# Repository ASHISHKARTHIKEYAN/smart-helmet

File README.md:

View this project on [CADLAB.io](https://cadlab.io/project/29150). 

# smart-helmet

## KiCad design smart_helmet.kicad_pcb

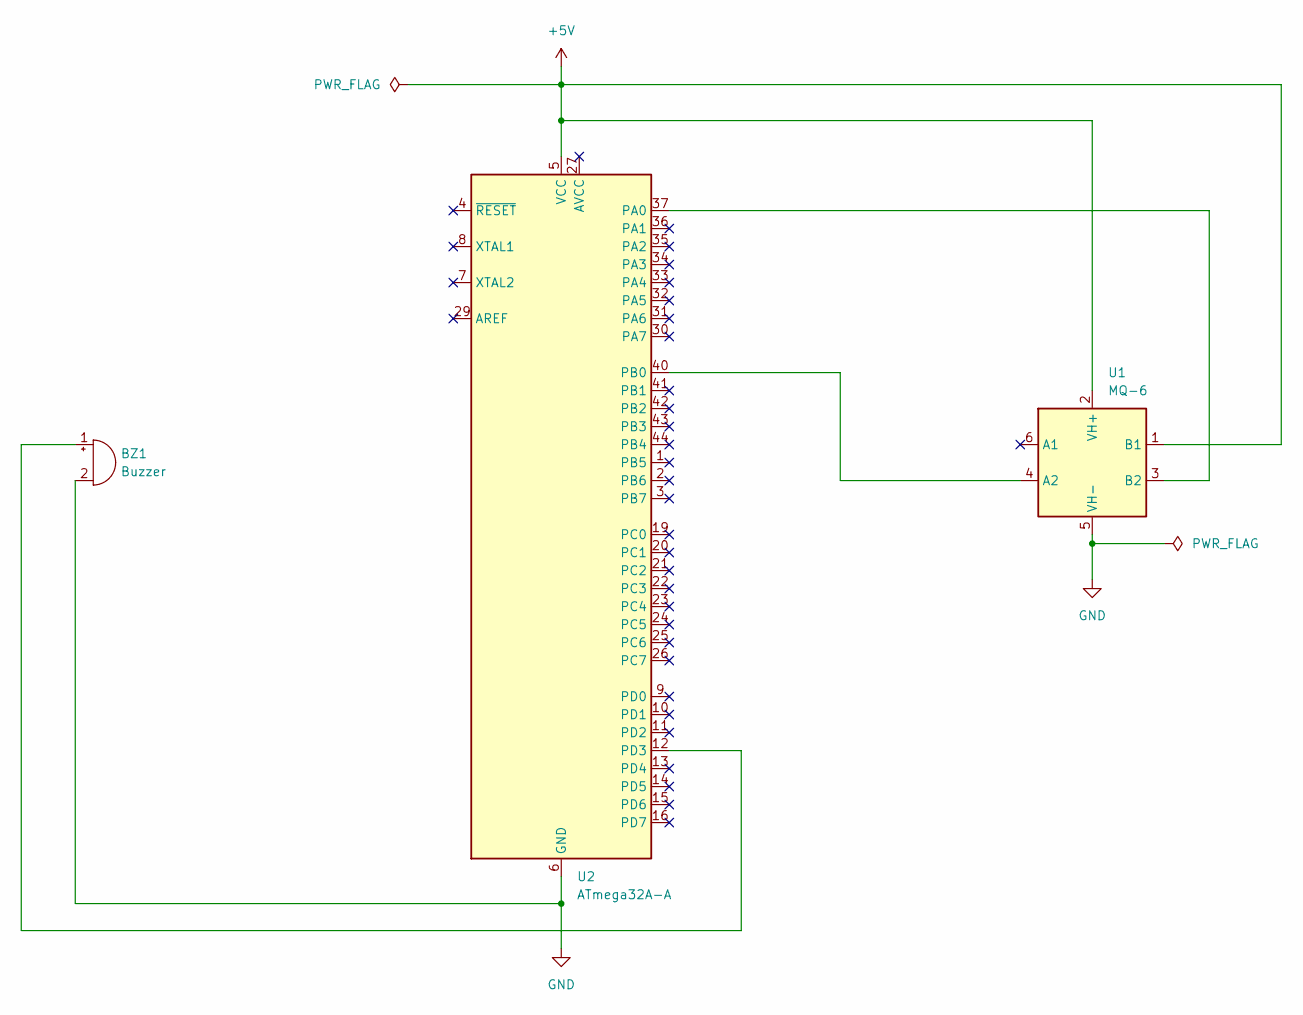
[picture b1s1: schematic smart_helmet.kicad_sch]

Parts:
BZ1: Buzzer; Buzzer_12x9.5RM7.6
U1: MQ-6
U2: ATmega32A-A; TQFP-44_10x10mm_P0.8mm

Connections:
+5V: U1.1 (B1), U1.2 (VH+), U2.5 (VCC), U2.17 (VCC), U2.38 (VCC)
GND: BZ1.2 (-), U1.5 (VH-), U2.6 (GND), U2.18 (GND), U2.28 (GND), U2.39 (GND)
unnamed: BZ1.1 (+), U2.12 (PD3)
unnamed: U1.4 (A2), U2.40 (PB0)
unnamed: U1.3 (B2), U2.37 (PA0)

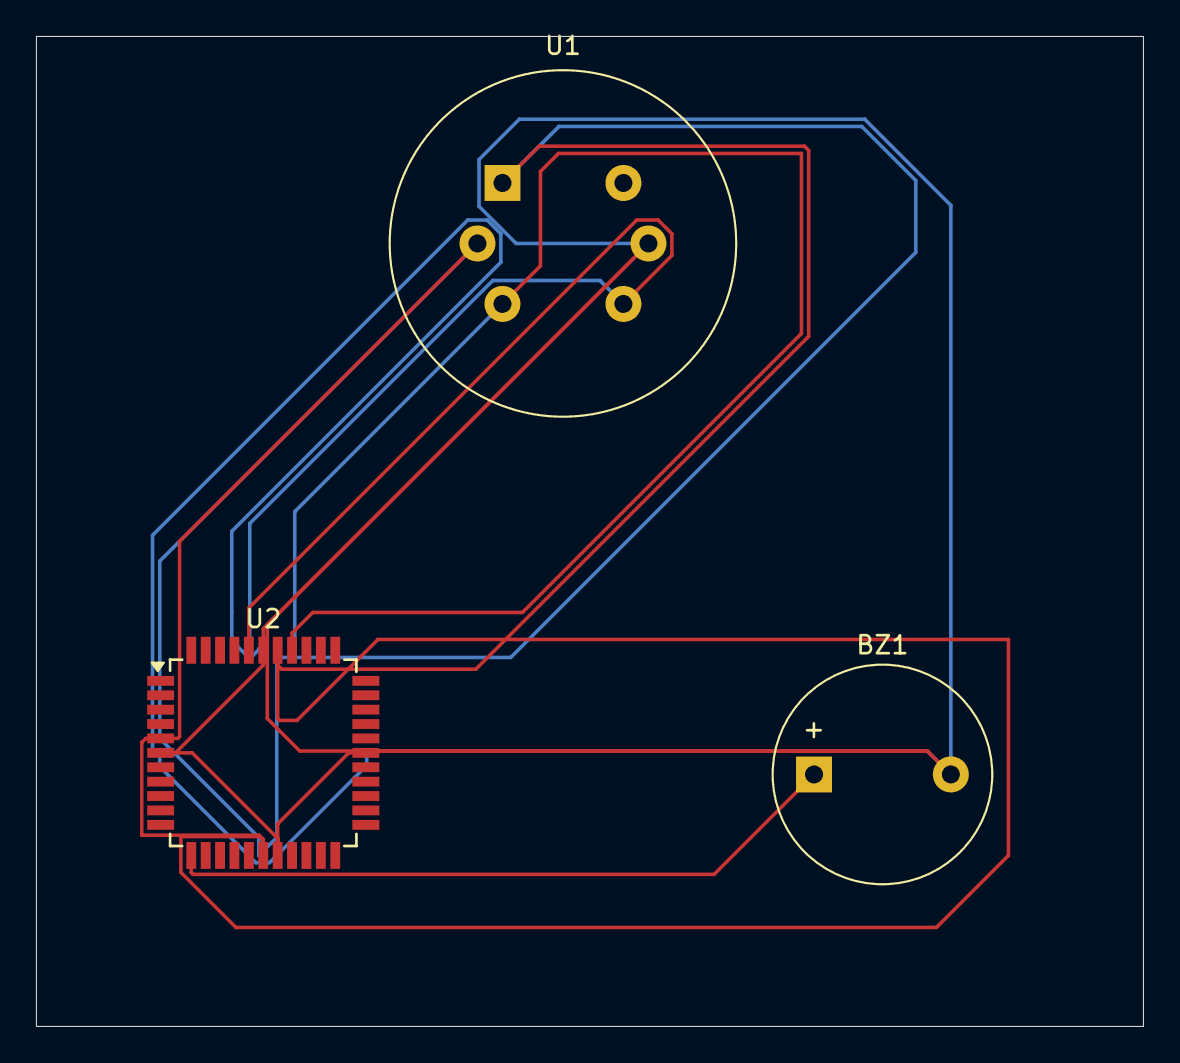
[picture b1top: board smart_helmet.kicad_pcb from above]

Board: 2 copper layers, 61.5 x 55.0 mm, 3 parts (0 on the bottom side), 5 nets.

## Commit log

2025-04-02 Normalize line endings
2025-04-02 Backlink to CADLAB.io has been added.
